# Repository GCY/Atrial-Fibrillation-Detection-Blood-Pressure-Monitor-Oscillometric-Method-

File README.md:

# Atrial-Fibrillation-Detection-Blood-Pressure-Monitor-Oscillometric-Method-
This project is electronic blood pressure monitor research platform with Oscillometric method, include SBP and DBP estimate algorithm, Atrial Fibrillation detection algorithm, calibration curve, GUI tool for fine-tune BP algorithm...etc, ofcourse, this is research use only.

## Blood Pressure Measurement Oscillometric Method

The oscillometric method was first demonstrated in 1876 and involves the observation of oscillations in the sphygmomanometer cuff pressure which are caused by the oscillations of blood flow, It uses a sphygmomanometer cuff, like the auscultatory method, but with an electronic pressure sensor (transducer) to observe cuff pressure oscillations, electronics to automatically interpret them, and automatic inflation and deflation of the cuff. The pressure sensor should be calibrated periodically to maintain accuracy.

A new analysis of relevant anatomy, physiology and physics reveals the mechanisms underlying the production of cuff pressure oscillations as well as a way to extract systolic and diastolic pressures from the envelope of oscillations in any individual subject. Stiffness characteristics of the compressed artery segment can be extracted from the envelope shape to create an individualized mathematical model. The model is tested with a matrix of possible systolic and diastolic pressure values, and the minimum least squares difference between observed and predicted envelope functions indicates the best fit choices of systolic and diastolic pressure within the test matrix.

In practice the different methods do not give identical results; an algorithm and experimentally obtained coefficients are used to adjust the oscillometric results to give readings which match the auscultatory results as well as possible. Accurate extraction of systolic and diastolic pressures from the envelope of cuff pressure oscillations remains an open problem in biomedical engineering. Since many oscillometric devices have not been validated, caution must be given as most are not suitable in clinical and acute care settings.

via [wiki.](https://en.wikipedia.org/wiki/Blood_pressure_measurement)

## Features
- [x] Blood Pressure Measurment - Systolic, Diastolic, Mean
- [x] Atrial Fibrillation Detection - Irregular Pulse Peak , Irregular Heart Beats
- [x] GUI Toos - Algorithm Finetune
- [x] ADC Clibration to Mercury Manometer Pressure - Polynomial Curve Fit
- [x] RAW Data Record

## Hardware

Project create is Eagle PCB 8.1.0 .</br>

<strong>V2 version, D1(BAT20) should be replaced with zero ohm resistor.</strong></br>

### Key Component List

- Electronics
  - TB6612FNG (for PUMP and VALVE PID control)
  - MPS-3117-006GC A2/A3(MEMS Wheatstone Bridge)
- Mechatronic
  - 3V DC Air Pump Motor(JQB032-3A or DQB030-A-3V)
  - 3V DC Electric Solenoid Valve(JQF1-3C1/DC3V Mini 10mm*15mm)
- Cuff and Tubing
  - 2mm*4mm Silicone Rubber Tubing x 2(20cm~30cm, for wrist cuff input and output)
  - 2mm*4mm Silicone Rubber Tubing x 3(5cm~10cm, for T Type connector)
  - 2mm*3mm T Type Plastic Barbed Connector
  - 2mm*3mm Straight Plastic Barbed Connector x 3
  - Wrist Air Cuff Input/Output(2 pinhole 2mm~3mm)
  
### Configure for Motor Electric Drives With Independent Power Supply - Battery2(U$19)
- J1, J2 pin1 connect to pin2 - battery2 charge
- J1, J2 pin2 connect to pin3 - motor drive with independent power supply
- JP1 pin1 connect to pin2 - motor drive with VCC
- JP1 pin2 connect to pin3 - motor drive with independent power supply

## Firmware

### Build and Burn The .elf
- 1.cd src/BPM
- 2.make
- 3.load main.elf

### Key Parameters

PWM_Freq is DC Motor PWM frequency.</br>
TIM_Prescaler = (168M/2)/1M = 84M</br>
TIM_Period = TIMER_PWM_MAX/PWM_Freq = 1000</br>

TIM = 84M / TIM_Prescaler = 1M</br>
TIM = 1M / TIM_ClockDivision = 1M</br>
1M / (TIM_Period + 1) = 1000Hz (1ms)</br>
<pre><code>
const uint16_t PWM_Freq = 1000;
</code></pre>

ARR = TIMER_PWM_MAX;</br>
CCR = 0 to TIMER_PWM_MAX = 0 to 100% PWM.</br>
In this case, PID PWM step 1 to 100 mapped to 100000 to 1000000.</br>
TIMER_PWM_33 and TIMER_PWM_40 is 33% and 40% PWM for calibration hand control.</br>
<pre><code>
const uint32_t PID_PWM_MIN = 1;
const uint32_t PID_PWM_MAX = 100;
const uint32_t TIMER_PWM_MIN = 100000;
const uint32_t TIMER_PWM_MAX; = 1000000;
const uint32_t TIMER_PWM_33 = 330000;
const uint32_t TIMER_PWM_40 = 400000;
</code></pre>

This is PID parameter, you need to redefine in ResetMeasurementParameter() function.</br>
<pre><code>
Kp = 2, Ki = 0.3, Kd = 0.001; // for JQB032-3A
</code></pre>

AC signal amplitude point of Systolic and Diastolic BP.</br>
<pre><code>
float as_am_value = 0.65f;
float ad_am_value = 0.7f;
</code></pre>

Polynomial curve fitting is generated from 『Calibration ADC-DC to Mercury Manometer Pressure』, you'll need to create 『curve.csv』and execute PC-GUI software main.app or BPM.exe in the same folder, it will output the『equation.txt』.</br>
e.g. degree = 2, equation.txt format is : (-1.0620516546)x^0+(0.1262915457)x^1+(-0.0000012119)x^2 </br>
<pre><code>
float a[3] = {-0.0000012119f,0.1262915457f,-1.0620516546f};
</code></pre>

If pulse_value_N / total_pulse_value_mean > IPP_Ratio, pulse_N is irregular pulse peak, and IPP ratio range 15%~25%.</br>
If IPP number / total_pulse_number > IHB_Ratio, this measurement is irregular heart beat.</br>
If two or more IHB of the three BP measurements, AF detected.<br>
<pre><code>
const float IPP_Ratio = 0.2f;
const float IHB_Ratio = 0.2f;
</code></pre>

### Operation Flowchart

### DC/AC Signal Process Flowchart

### Measurment Flowchart

### BPM Mode Demo

## Software

### AFib-BPM GUI Demo

### Build
- Win10
  - 1.Open BPM.sln
  - 2.Rebuild
- Mac High Sierra
  - 1.make
  
### Dependence
- Win10
  - wxWidgets 3.1.2
  - VS2017 - MSVC 10.0.17763-SDK
- Mac High Sierra
  - wxWidgets 3.x
  - g++

### Parameters Setup
When burning the firmware for the first time, you must set the PID control and blood pressure algorithm parameters. After the PC-Host and VCP are successfully connected, select the Tuning menu to adjust the parameters.</br>

Display the parameters that have been set. If the parameters are unset, the value is "0xFFFFFFFF" in sector11 of flash. The PID parameters shown in the figure need to be divided by hundred. (for example, P = 290, in firmware, P is 2.9 .)</br>

### Mac High Sierra GUI

### Win10 GUI

### Operation Manual
- Menu Tools -> VCP is connect to device.
- "Ad/Am" and "As/Am" text box is Diastolic and Systolic BP Point of AC signal amplitude.
- "Measurment" button is BP measurment after VCP connected.
- "USB Mode" button is switch from "USB Mode"(Measurment) to "Calibration Mode", and vice versa.
- "Pressurize" and "Leak" button for control mercury manometer high and low in calibration mode.

## Oscillometric Method
The two chart below show AC signal types, all of types are correct.

### Type1 AC Signal

### Type2 AC Signal

## Calibration ADC-DC to Mercury Manometer Pressure

Pressure calibration reference is Mercury Manometer(Sphygmomanometer) or Aneroid Sphygmomanometer, you can buy products from Yuwell, Welch Allyn...etc </br>

### PC-GUI Software Control Steps
- 1.Connecting device and PC-GUI software.
- 2.Click USB Mode button switch to Calibration Mode, after this, OLED display show you ADC0 value per-second.
- 3.Control Mercury Manometer high and low with Presurize and Leak button.
- 4.Record Mercury Manometer pressure point and OLED ADC0 value to 『curve.csv』file, at least 10-points and pressure range 0~250mmHg. 
- 5.checking curve.csv is located in the same folder as the PC-GUI software.
- 6.Close PC-GUI software than reopen it, it will generate the『equation.txt』.
- 7.copy equation and replace firmware parameter 『float a[3]』 in main.c.

Column A is ADC0-value, B is Mercury Manometer mmHg pressure.</br>

## Atrial Fibrillation In Oscillometric Method Detect Algorithm

Below are a few real world cases of the AFib(for example PCV, PAC), envelope wave lost some peaks.</br>

### Premature Atrial Contractions

### Premature Ventricular Contractions

## Reference
- Kabutoya, T., Imai, Y., Hoshide, S., & Kario, K. (2017). Diagnostic accuracy of a new algorithm to detect atrial fibrillation in a home blood pressure monitor. The Journal of Clinical Hypertension, 19(11), 1143-1147.

- Ogedegbe, G., & Pickering, T. (2010). Principles and techniques of blood pressure measurement. Cardiology clinics, 28(4), 571-586.

- Babbs, C. F. (2012). Oscillometric measurement of systolic and diastolic blood pressures validated in a physiologic mathematical model. Biomedical engineering online, 11(1), 56.

- Geddes, L. A., Voelz, M., Combs, C., Reiner, D., & Babbs, C. F. (1982). Characterization of the oscillometric method for measuring indirect blood pressure. Annals of biomedical engineering, 10(6), 271-280.

- C++ Program for Polynomial Fit (Least Squares) : https://www.bragitoff.com/2015/09/c-program-for-polynomial-fit-least-squares/

LICENSE
-------

MIT License

Copyright (c) 2019 Tony Guo

Permission is hereby granted, free of charge, to any person obtaining a copy
of this software and associated documentation files (the "Software"), to deal
in the Software without restriction, including without limitation the rights
to use, copy, modify, merge, publish, distribute, sublicense, and/or sell
copies of the Software, and to permit persons to whom the Software is
furnished to do so, subject to the following conditions:

The above copyright notice and this permission notice shall be included in all
copies or substantial portions of the Software.

THE SOFTWARE IS PROVIDED "AS IS", WITHOUT WARRANTY OF ANY KIND, EXPRESS OR
IMPLIED, INCLUDING BUT NOT LIMITED TO THE WARRANTIES OF MERCHANTABILITY,
FITNESS FOR A PARTICULAR PURPOSE AND NONINFRINGEMENT. IN NO EVENT SHALL THE
AUTHORS OR COPYRIGHT HOLDERS BE LIABLE FOR ANY CLAIM, DAMAGES OR OTHER
LIABILITY, WHETHER IN AN ACTION OF CONTRACT, TORT OR OTHERWISE, ARISING FROM,
OUT OF OR IN CONNECTION WITH THE SOFTWARE OR THE USE OR OTHER DEALINGS IN THE
SOFTWARE.

OSHW Certification
-------

https://certification.oshwa.org/tw000002.html

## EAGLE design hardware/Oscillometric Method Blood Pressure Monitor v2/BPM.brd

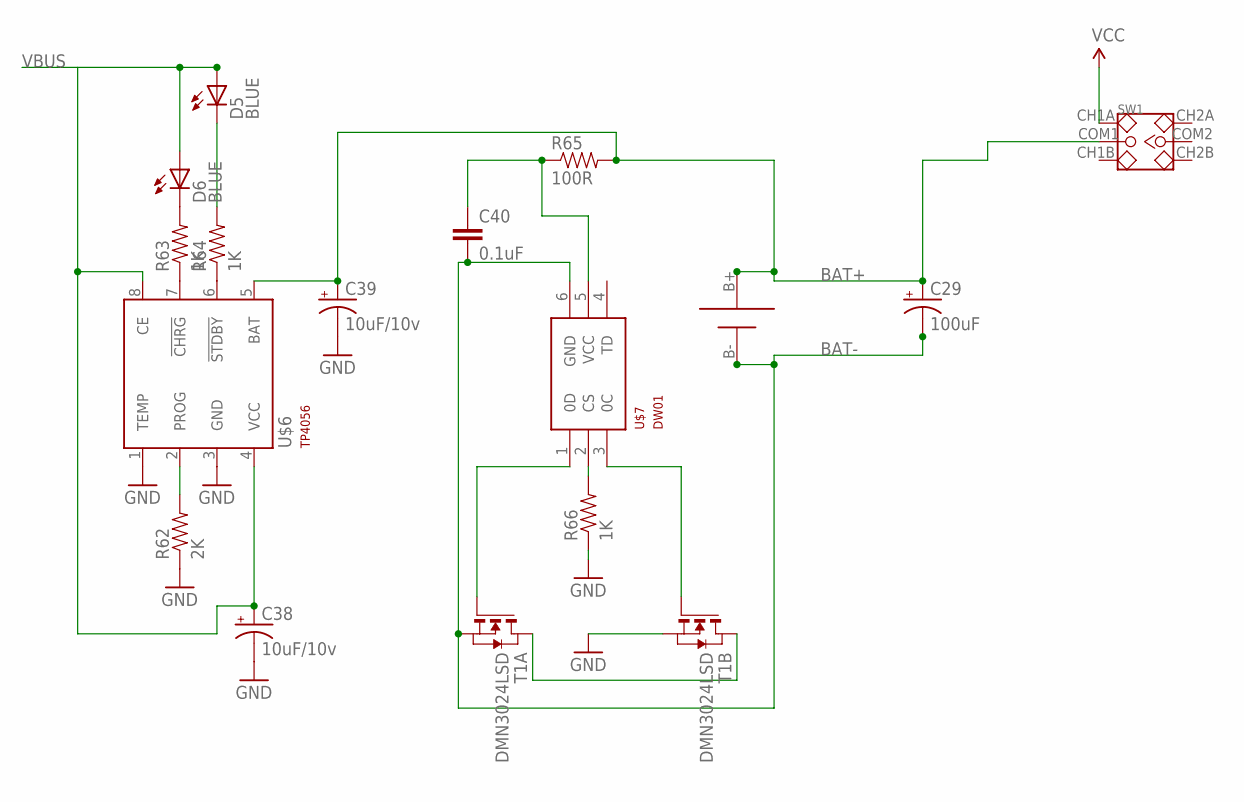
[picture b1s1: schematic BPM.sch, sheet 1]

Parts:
C29: 100uF; NIPPON_F80
C38, C39: 10uF/10v; EIA3216-KIT
C40: 0.1uF; 0603-CAP
D5, D6: BLUE; LED-0603
R62: 2K; 0603-RES
R63, R64, R66: 1K; 0603-RES
R65: 100R; 0603-RES
SW1: SMD-TOGGLE-SWITCH-2CH(2X3P-7X3.5MM); SW6-2.54-SMD-7.0X3.5X1.5MM
T1: DMN3024LSD; TSSOP-8
U$4: 18650SMD
U$6: TP4056; SOT23-8
U$7: DW01; SOT23-6

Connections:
BAT+: C29.+, C39.A (+), R65.2, SW1.COM1, U$4.B+, U$6.5 (BAT); also elsewhere on the board
BAT-: C29.-, C40.2, T1.2 (S), T1.3 (S), U$4.B-, U$7.6 (GND); also elsewhere on the board
GND: C38.C (-), C39.C (-), R62.1, R66.1, T1.6 (S), T1.7 (S), U$6.1 (TEMP), U$6.3 (GND); also elsewhere on the board
unnamed: R62.2, U$6.2 (PROG)
unnamed: R63.1, U$6.7 (!CHRG)
unnamed: R64.1, U$6.6 (!STDBY)
unnamed: D6.C, R63.2
unnamed: D5.C, R64.2
unnamed: C40.1, R65.1, U$7.5 (VCC)
unnamed: T1.4 (G), U$7.1 (0D)
unnamed: R66.2, U$7.2 (CS)
unnamed: T1.1 (D), T1.8 (D)
unnamed: T1.5 (G), U$7.3 (0C)
VBUS: C38.A (+), D5.A, D6.A, U$6.4 (VCC), U$6.8 (CE); also elsewhere on the board
VCC: SW1.CH1A; also elsewhere on the board

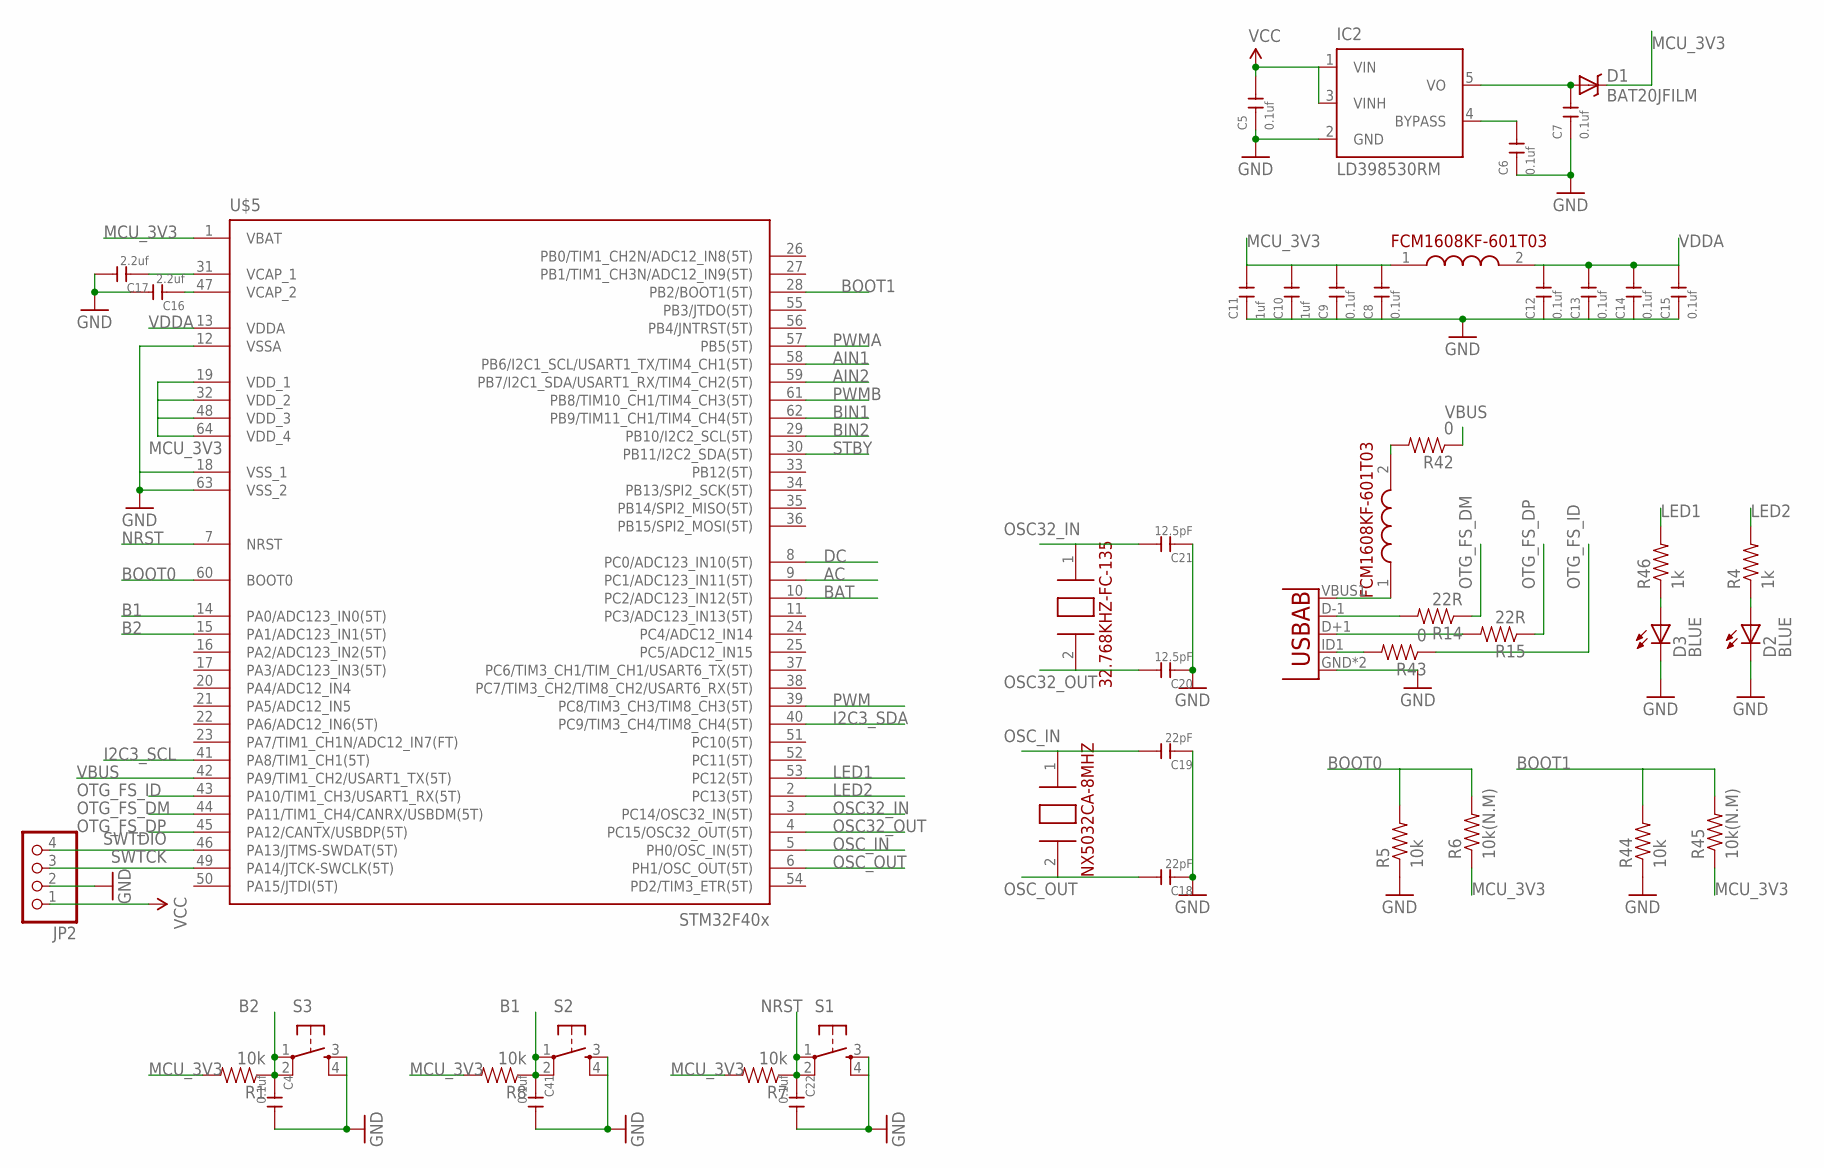
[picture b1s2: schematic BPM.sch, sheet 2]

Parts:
C4, C5, C6, C7, C8, C9, C12, C13, C14, C15, C22, C41: 0.1uf; C0603
C10, C11: 1uf; C0603
C16, C17: 2.2uf; C0603
C18, C19: 22pF; C0603
C20, C21: 12.5pF; C0603
D1: BAT20JFILM; SOD-323
D2, D3: BLUE; LED-0603
IC2: LD398530RM; SOT23-5L
JP2: PINHD-1X4; 1X04
R1, R5, R7, R8, R44: 10k; 0603
R4, R46: 1k; 0603
R6, R45: 10k(N.M); 0603
R14, R15: 22R; 0603-RES
R42, R43: 0; 0603-RES
S1, S2, S3: TAC_SWITCHSMD; TACTILE_SWITCH_SMD
U1: USB""; USB-MICRO-SMD
U$5: STM32F405R; TQFP64
U$8: 32.768KHZ-FC-135
U$9: NX5032CA-8MHZ
U$10, U$15: FCM1608KF-601T03

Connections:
AC: U$5.9 (PC1/ADC123_IN11(5T)); also elsewhere on the board
AIN1: U$5.58 (PB6/I2C1_SCL/USART1_TX/TIM4_CH1(5T)); also elsewhere on the board
AIN2: U$5.59 (PB7/I2C1_SDA/USART1_RX/TIM4_CH2(5T)); also elsewhere on the board
B1: C41.1, R8.1, S2.1, S2.2, U$5.14 (PA0/ADC123_IN0(5T))
B2: C4.1, R1.1, S3.1, S3.2, U$5.15 (PA1/ADC123_IN1(5T))
BAT: U$5.10 (PC2/ADC123_IN12(5T)); also elsewhere on the board
BIN1: U$5.62 (PB9/TIM11_CH1/TIM4_CH4(5T)); also elsewhere on the board
BIN2: U$5.29 (PB10/I2C2_SCL(5T)); also elsewhere on the board
BOOT0: R5.2, R6.2, U$5.60 (BOOT0)
BOOT1: R44.2, R45.2, U$5.28 (PB2/BOOT1(5T))
DC: U$5.8 (PC0/ADC123_IN10(5T)); also elsewhere on the board
GND: C4.2, C5.1, C6.1, C7.1, C8.1, C9.1, C10.1, C11.1, C12.1, C13.1, C14.1, C15.1, C16.2, C17.2, C18.1, C19.1, C20.1, C21.1, C22.2, C41.2, D2.C, D3.C, IC2.2 (GND), JP2.2, R5.1, R44.1, S1.3, S1.4, S2.3, S2.4, S3.3, S3.4, U1.GND, U1.GND1 (GND), U$5.12 (VSSA), U$5.18 (VSS_1), U$5.63 (VSS_2); also elsewhere on the board
I2C3_SCL: U$5.41 (PA8/TIM1_CH1(5T)); also elsewhere on the board
I2C3_SDA: U$5.40 (PC9/TIM3_CH4/TIM8_CH4(5T)); also elsewhere on the board
LED1: R46.2, U$5.53 (PC12(5T))
LED2: R4.2, U$5.2 (PC13(5T))
MCU_3V3: C8.2, C9.2, C10.2, C11.2, D1.1 (C), R1.2, R6.1, R7.2, R8.2, R45.1, U$5.1 (VBAT), U$5.19 (VDD_1), U$5.32 (VDD_2), U$5.48 (VDD_3), U$5.64 (VDD_4), U$10.1 (1.IN); also elsewhere on the board
unnamed: D2.A, R4.1
unnamed: C17.1, U$5.31 (VCAP_1)
unnamed: C16.1, U$5.47 (VCAP_2)
unnamed: C6.2, IC2.4 (BYPASS)
unnamed: C7.2, D1.2 (A), IC2.5 (VO)
unnamed: R14.2, U1.D-1 (D-)
unnamed: R15.2, U1.D+1 (D+)
unnamed: R43.2, U1.ID1 (USBID)
unnamed: U1.VBUS1 (VBUS), U$15.1 (1.IN)
unnamed: R42.2, U$15.2 (2.OUT)
unnamed: D3.A, R46.1
NRST: C22.1, R7.1, S1.1, S1.2, U$5.7 (NRST)
OSC32_IN: C21.2, U$5.3 (PC14/OSC32_IN(5T)), U$8.1 (1.XIN)
OSC32_OUT: C20.2, U$5.4 (PC15/OSC32_OUT(5T)), U$8.2 (2.XIN)
OSC_IN: C19.2, U$5.5 (PH0/OSC_IN(5T)), U$9.1 (1.XIN)
OSC_OUT: C18.2, U$5.6 (PH1/OSC_OUT(5T)), U$9.2 (2.XOUT)
OTG_FS_DM: R14.1, U$5.44 (PA11/TIM1_CH4/CANRX/USBDM(5T))
OTG_FS_DP: R15.1, U$5.45 (PA12/CANTX/USBDP(5T))
OTG_FS_ID: R43.1, U$5.43 (PA10/TIM1_CH3/USART1_RX(5T))
PWM: U$5.39 (PC8/TIM3_CH3/TIM8_CH3(5T)); also elsewhere on the board
PWMA: U$5.57 (PB5(5T)); also elsewhere on the board
PWMB: U$5.61 (PB8/TIM10_CH1/TIM4_CH3(5T)); also elsewhere on the board
STBY: U$5.30 (PB11/I2C2_SDA(5T)); also elsewhere on the board
SWTCK: JP2.3, U$5.49 (PA14/JTCK-SWCLK(5T))
SWTDIO: JP2.4, U$5.46 (PA13/JTMS-SWDAT(5T))
VBUS: R42.1, U$5.42 (PA9/TIM1_CH2/USART1_TX(5T)); also elsewhere on the board
VCC: C5.2, IC2.1 (VIN), IC2.3 (VINH), JP2.1; also elsewhere on the board
VDDA: C12.2, C13.2, C14.2, C15.2, U$5.13 (VDDA), U$10.2 (2.OUT)

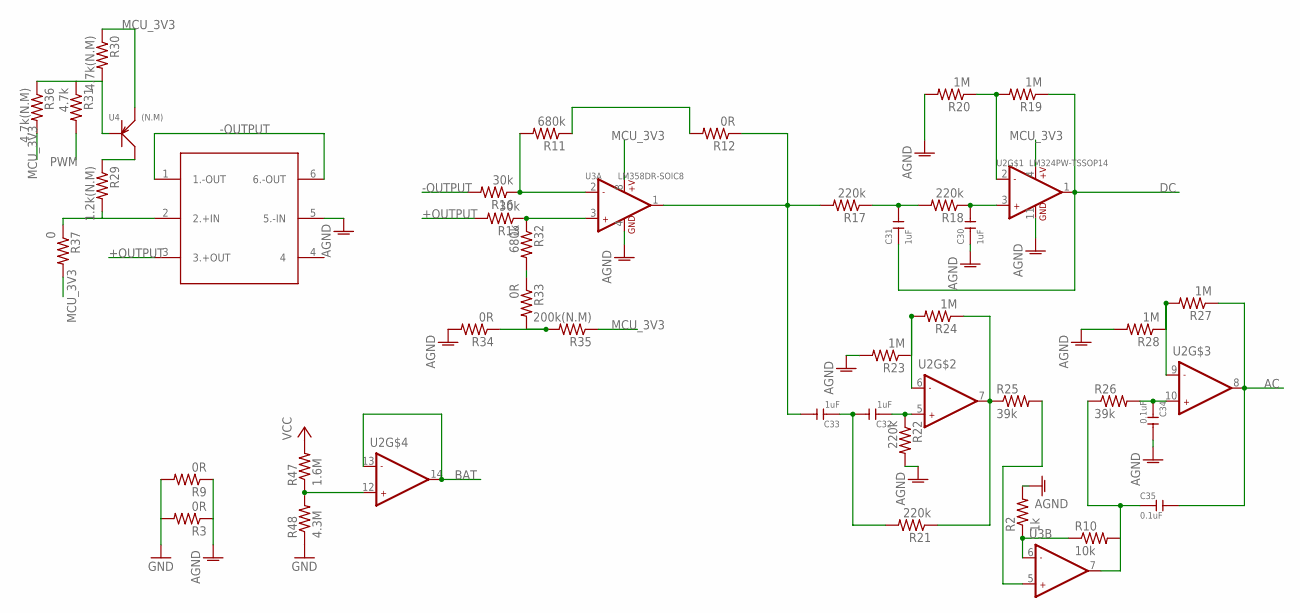
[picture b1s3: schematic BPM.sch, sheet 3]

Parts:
C30, C31, C32, C33: 1uF; C0603
C34, C35: 0.1uF; C0603
R2: 1k; 0603
R3, R9, R12, R33, R34: 0R; 0603
R10: 10k; 0603
R11, R32: 680k; 0603
R13, R16: 30k; 0603
R17, R18, R21, R22: 220k; 0603
R19, R20, R23, R24, R27, R28: 1M; 0603
R25, R26: 39k; 0603
R29: 1.2k(N.M); 0603
R30, R36: 4.7k(N.M); 0603
R31: 4.7k; 0603
R35: 200k(N.M); 0603
R37: 0; 0603
R47: 1.6M; 0603
R48: 4.3M; 0603
U2: LM324PW-TSSOP14; TSSOP14-0.65-5X4.4MM
U3: LM358DR-SOIC8; SOIC8-1.27-5X4MM
U4: (N.M); SOT-23
U$1: MPS-3117-006G

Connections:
+OUTPUT: R13.2, U$1.3 (3.+OUT)
-OUTPUT: R16.2, U$1.1 (1.-OUT), U$1.6 (6.-OUT)
AC: C35.2, R27.1, U2.8 (OUT2); also elsewhere on the board
AGND: C30.1, C34.2, R2.2, R3.1, R9.1, R20.2, R22.2, R23.2, R28.2, R34.2, U2.11 (GND), U3.4 (GND), U$1.5 (5.-IN)
BAT: U2.13 (-IN2), U2.14 (OUT2); also elsewhere on the board
DC: C31.1, R19.1, U2.1 (OUT1); also elsewhere on the board
GND: R3.2, R9.2, R48.1; also elsewhere on the board
MCU_3V3: R30.1, R35.1, R36.2, R37.2, U2.4 (+V), U3.8 (+V), U4.2 (E); also elsewhere on the board
unnamed: C35.1, R10.2, R26.1, U3.7 (OUT2)
unnamed: R25.2, U3.5 (+IN2)
unnamed: R47.1, R48.2, U2.12 (+IN2)
unnamed: R2.1, R10.1, U3.6 (-IN2)
unnamed: R11.1, R12.2
unnamed: R11.2, R16.1, U3.2 (-IN1)
unnamed: C33.2, R12.1, R17.2, U3.1 (OUT1)
unnamed: R13.1, R32.1, U3.3 (+IN1)
unnamed: R29.2, R37.1, U$1.2 (2.+IN)
unnamed: C31.2, R17.1, R18.2
unnamed: C30.2, R18.1, U2.3 (+IN1)
unnamed: C32.1, R22.1, U2.5 (+IN2)
unnamed: R19.2, R20.1, U2.2 (-IN1)
unnamed: C32.2, C33.1, R21.2
unnamed: R21.1, R24.1, R25.1, U2.7 (OUT2)
unnamed: R23.1, R24.2, U2.6 (-IN2)
unnamed: R29.1, U4.3 (C)
unnamed: C34.1, R26.2, U2.10 (+IN2)
unnamed: R32.2, R33.1
unnamed: R27.2, R28.1, U2.9 (-IN2)
unnamed: R30.2, R31.1, R36.1, U4.1 (B)
unnamed: R33.2, R34.1, R35.2
PWM: R31.2; also elsewhere on the board
VCC: R47.2; also elsewhere on the board

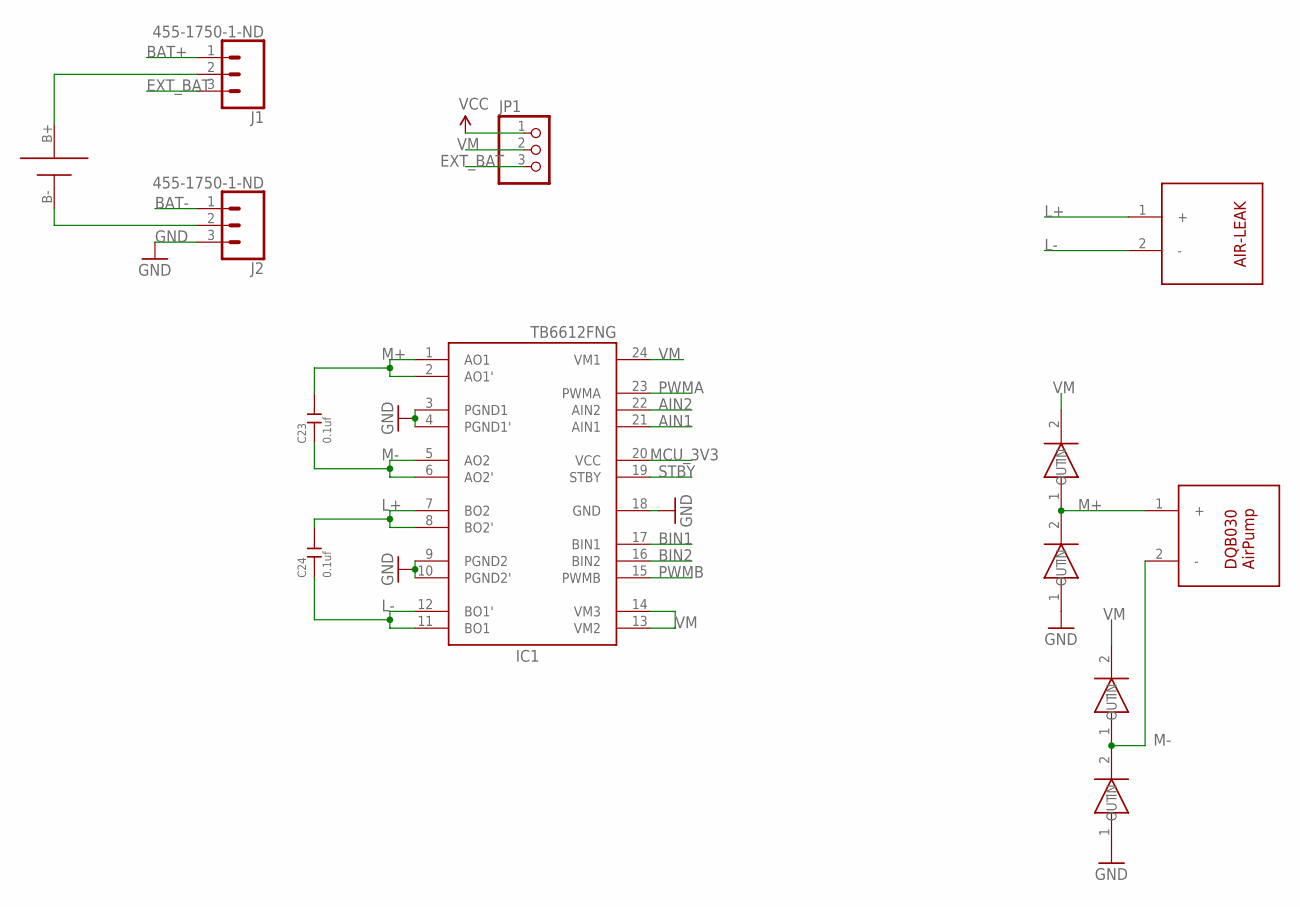
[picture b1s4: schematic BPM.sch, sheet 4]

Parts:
C23, C24: 0.1uf; C0603
IC1: TB6612FNG; SSOP24
J1, J2: 455-1750-1-ND; 1X03
JP1: PINHD-1X3; 1X03
U$11: AIR-LEAK
U$12: DQB030-AIRPUMP
U$13, U$14, U$16, U$17: SMA-SS34
U$19: 18650SMD

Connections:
AIN1: IC1.21 (AIN1); also elsewhere on the board
AIN2: IC1.22 (AIN2); also elsewhere on the board
BAT+: J1.1; also elsewhere on the board
BAT-: J2.1; also elsewhere on the board
BIN1: IC1.17 (BIN1); also elsewhere on the board
BIN2: IC1.16 (BIN2); also elsewhere on the board
EXT_BAT: J1.3, JP1.3
GND: IC1.3 (PGND1), IC1.4 (PGND1'), IC1.9 (PGND2), IC1.10 (PGND2'), IC1.18 (GND), J2.3, U$14.1 (IN), U$17.1 (IN); also elsewhere on the board
L+: C24.2, IC1.7 (BO2), IC1.8 (BO2'), U$11.1 (+)
L-: C24.1, IC1.11 (BO1), IC1.12 (BO1'), U$11.2 (-)
M+: C23.2, IC1.1 (AO1), IC1.2 (AO1'), U$12.1 (+), U$13.1 (IN), U$14.2 (OUT)
M-: C23.1, IC1.5 (AO2), IC1.6 (AO2'), U$12.2 (-), U$16.1 (IN), U$17.2 (OUT)
MCU_3V3: IC1.20 (VCC); also elsewhere on the board
unnamed: J1.2, U$19.B+
unnamed: J2.2, U$19.B-
PWMA: IC1.23 (PWMA); also elsewhere on the board
PWMB: IC1.15 (PWMB); also elsewhere on the board
STBY: IC1.19 (STBY); also elsewhere on the board
VCC: JP1.1; also elsewhere on the board
VM: IC1.13 (VM2), IC1.14 (VM3), IC1.24 (VM1), JP1.2, U$13.2 (OUT), U$16.2 (OUT)

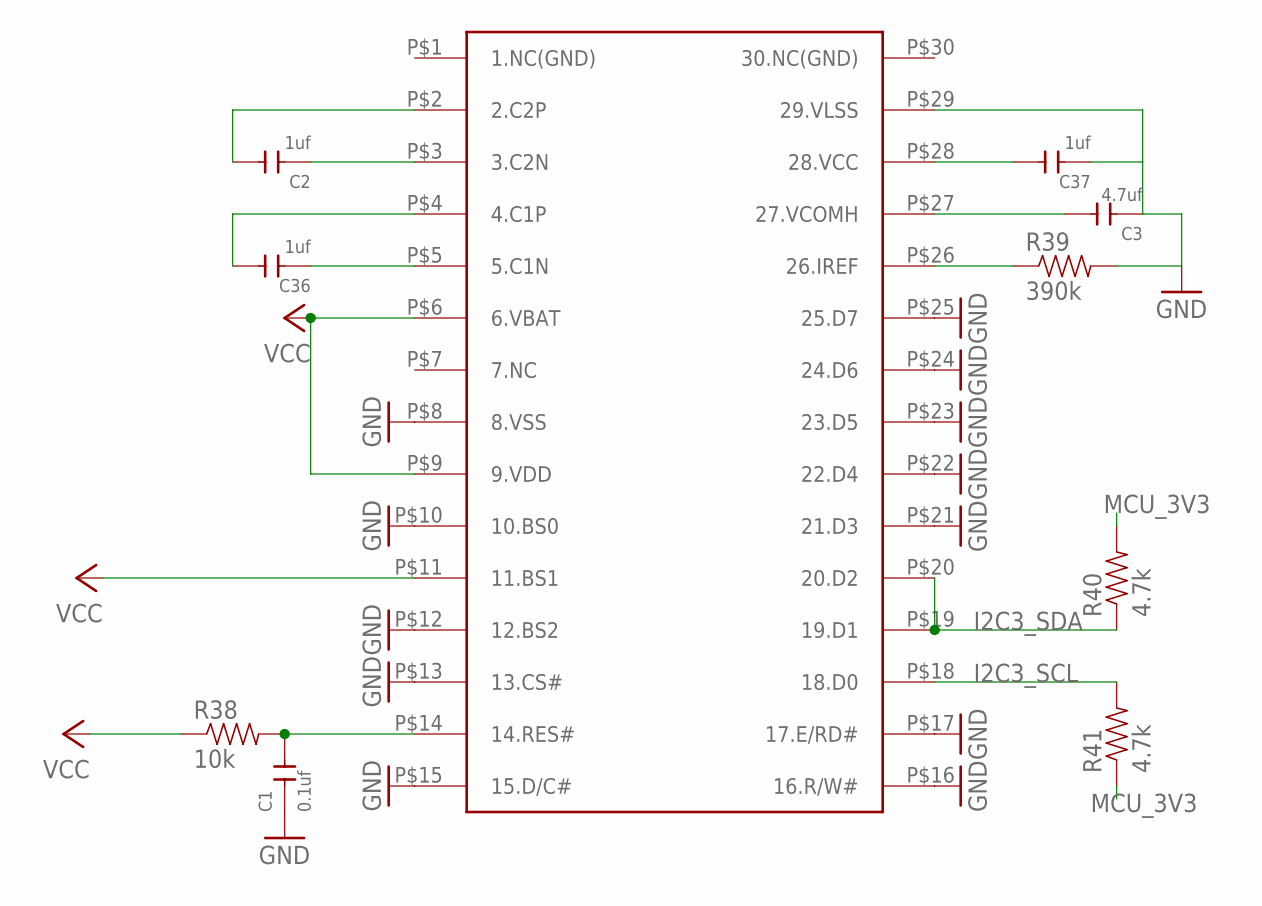
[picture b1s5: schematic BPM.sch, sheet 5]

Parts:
C1: 0.1uf; C0603
C2, C36, C37: 1uf; C0603
C3: 4.7uf; C0603
R38: 10k; 0603
R39: 390k; 0603
R40, R41: 4.7k; 0603
U$18: ER-OLED0.96

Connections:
GND: C1.1, C3.1, C37.1, R39.2, U$18.P$8 (8.VSS), U$18.P$10 (10.BS0), U$18.P$12 (12.BS2), U$18.P$13 (13.CS#), U$18.P$15 (15.D/C#), U$18.P$16 (16.R/W#), U$18.P$17 (17.E/RD#), U$18.P$21 (21.D3), U$18.P$22 (22.D4), U$18.P$23 (23.D5), U$18.P$24 (24.D6), U$18.P$25 (25.D7), U$18.P$29 (29.VLSS); also elsewhere on the board
I2C3_SCL: R41.2, U$18.P$18 (18.D0); also elsewhere on the board
I2C3_SDA: R40.1, U$18.P$19 (19.D1), U$18.P$20 (20.D2); also elsewhere on the board
MCU_3V3: R40.2, R41.1; also elsewhere on the board
unnamed: C1.2, R38.2, U$18.P$14 (14.RES#)
unnamed: C2.1, U$18.P$3 (3.C2N)
unnamed: C36.1, U$18.P$5 (5.C1N)
unnamed: C2.2, U$18.P$2 (2.C2P)
unnamed: C36.2, U$18.P$4 (4.C1P)
unnamed: R39.1, U$18.P$26 (26.IREF)
unnamed: C3.2, U$18.P$27 (27.VCOMH)
unnamed: C37.2, U$18.P$28 (28.VCC)
VCC: R38.1, U$18.P$6 (6.VBAT), U$18.P$9 (9.VDD), U$18.P$11 (11.BS1); also elsewhere on the board

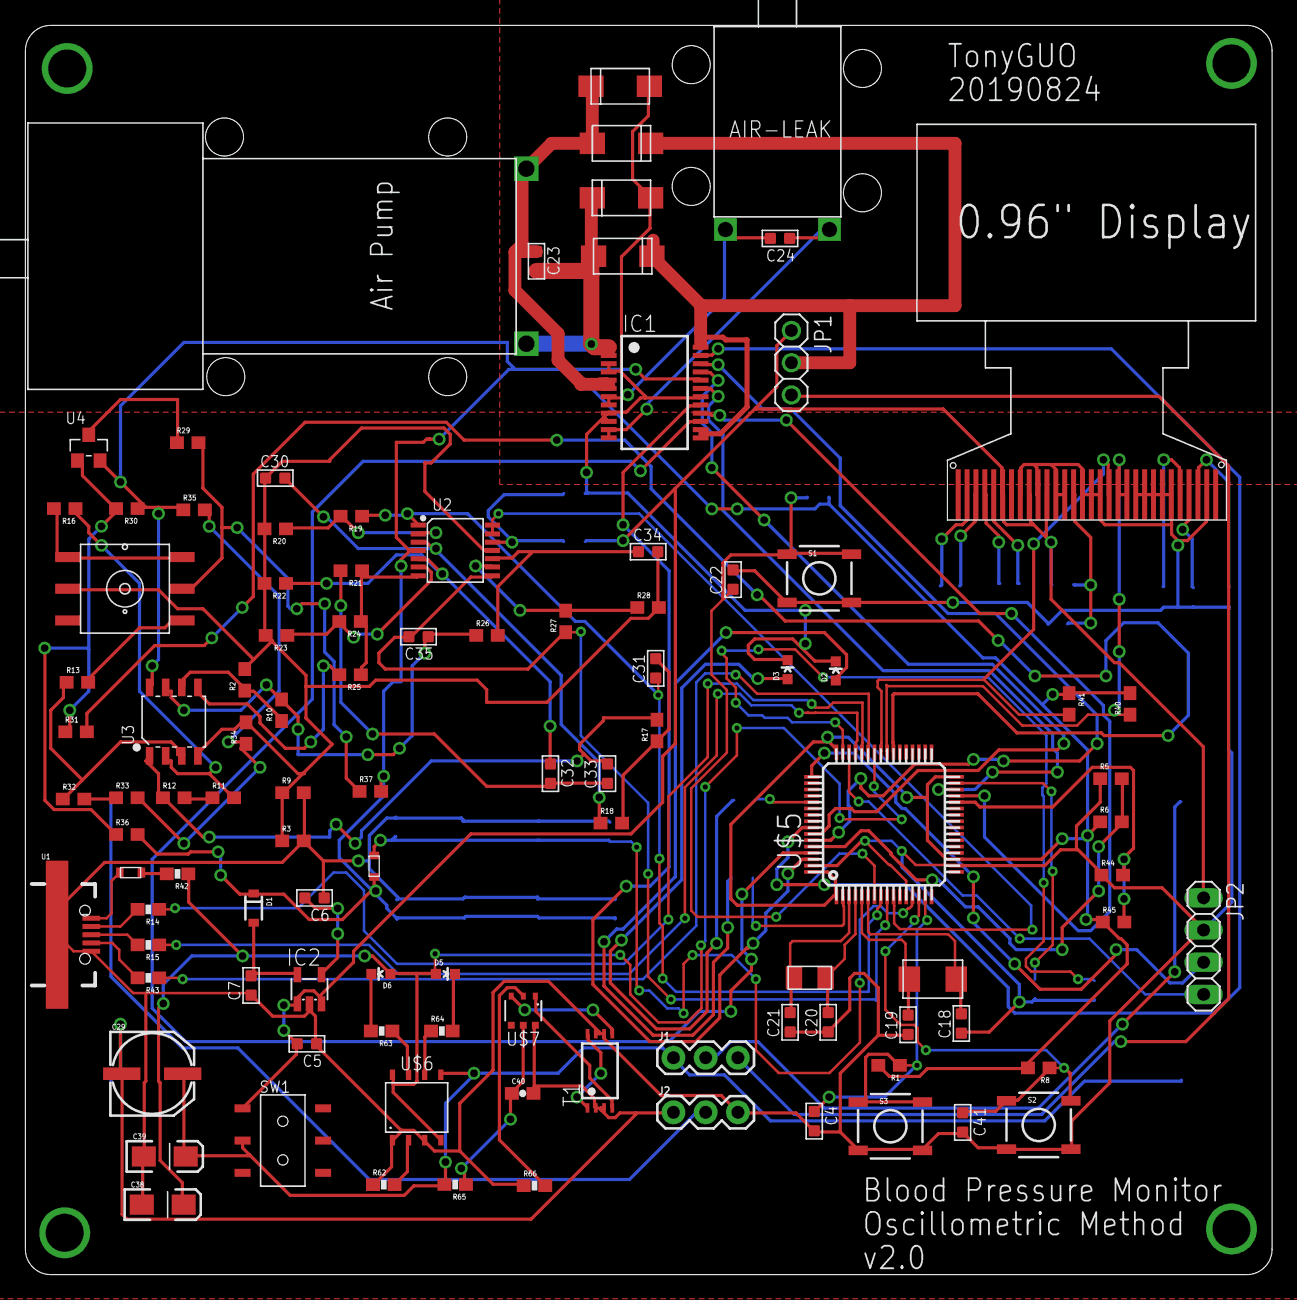
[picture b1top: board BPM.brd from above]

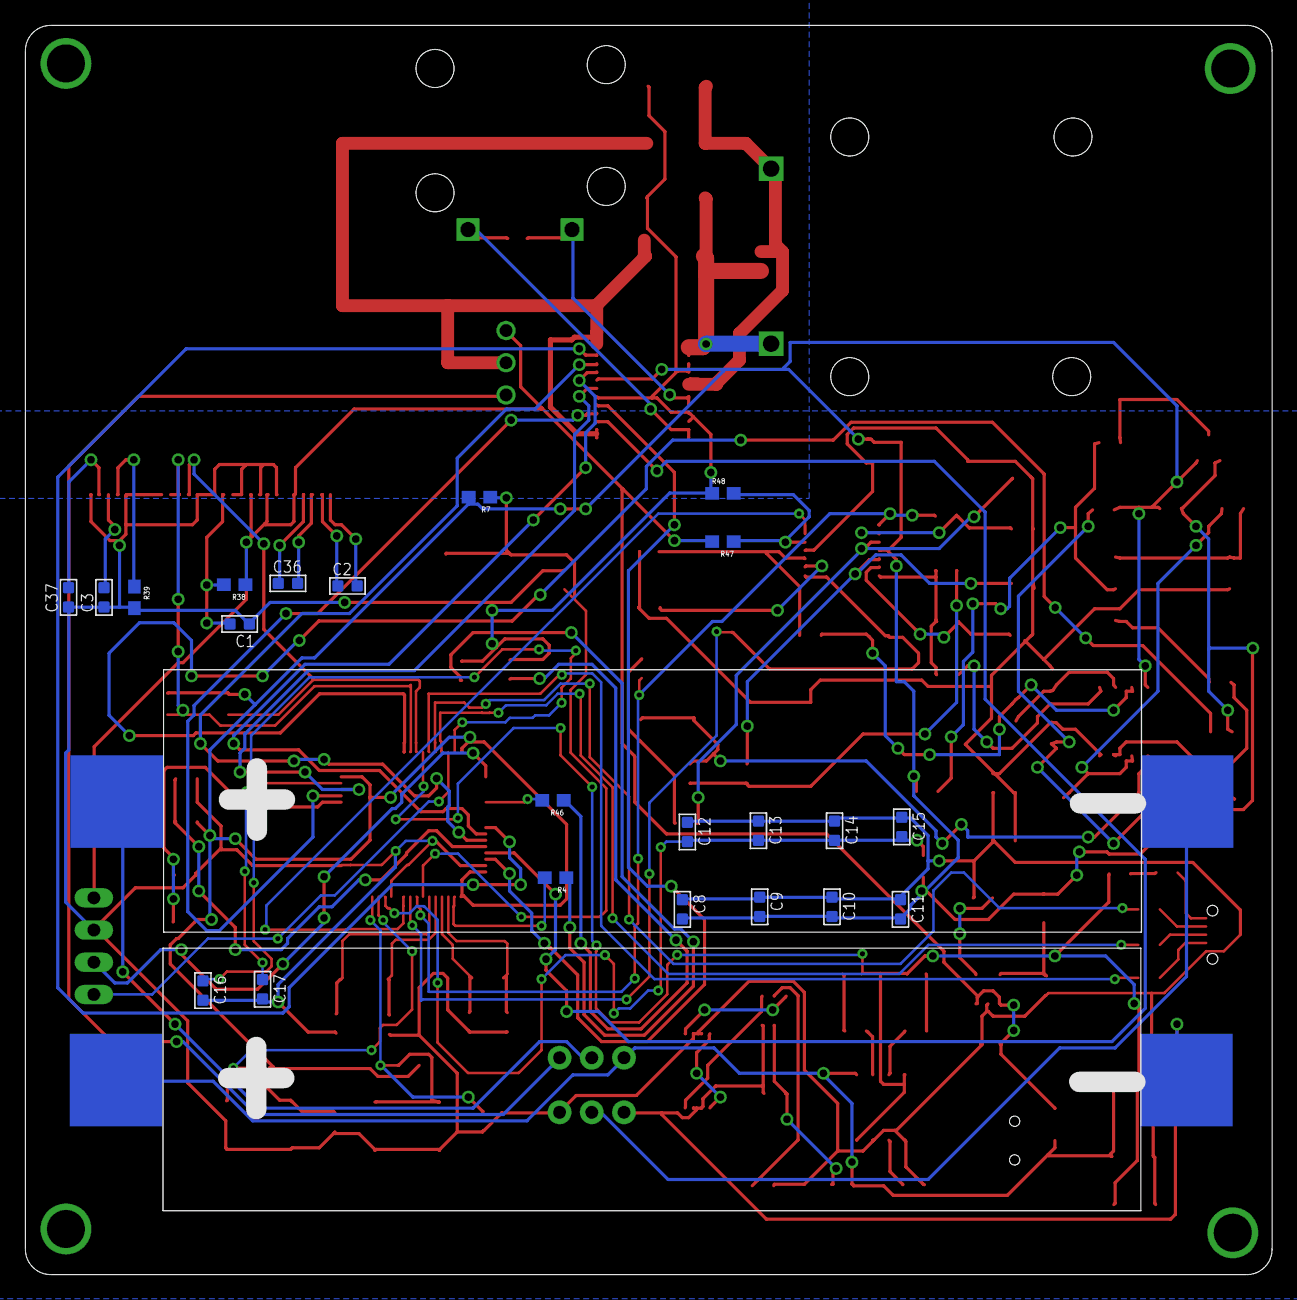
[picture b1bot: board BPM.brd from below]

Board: 2 copper layers, 98.3 x 98.5 mm, 127 parts (24 on the bottom side), 98 nets.

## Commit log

2019-10-02 picture
2019-10-13 AF Detect Algorithm
2019-10-16 PQRST
2019-10-17 assembly
2019-10-17 t-type and direct connector
2019-11-03 MAC GUI
2019-11-03 WIN10 GUI
2019-11-03 Eagle PCB - AF-BPM v2
2019-11-03 GUI Software
2019-11-03 STM32F405 Firmware
2019-11-06 flowchart
2019-11-09 compress
2019-11-09 fixed diastolic mark bug
2019-11-10 calibration example
2019-11-13 OSHW Logo
2019-11-17 Fixed curve.csv path
2019-11-18 .cs -> .csv
2020-01-12 Mercury Mode
2020-06-11 add include arm_math
2021-03-06 usb_desc for win10
2021-03-06 Win10 PC-HOST
2021-10-14 Add new function for parameters tuning
2021-10-14 edit res
2021-10-14 edit readme
2024-12-28 edit VCP

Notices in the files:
parts and their libraries:
SparkFun-Capacitors: Licensing: CC v3.0 Share-Alike You are welcome to use this library for commercial purposes.
SparkFun-Connectors: Licensing: Creative Commons ShareAlike 4.0 International - https://creativecommons.org/licenses/by-sa/4.0
